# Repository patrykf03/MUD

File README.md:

# The MUD Project

## Warning
**The entire project is untested, use at your own risk and look over whether its not broken beforehand.**

<br/>
The Multiple Universal Daughterboard project is a series of pcb's I've designed to have replaceable modules with microcontrollers.

There are 2 modules based on STM32F411 and nRF microcontrollers.

They can be integrated either by putting an M.2 connector directly on the pcb or connected from a daughterboard over a 30 pin flat ribbon connector.

There are 2 daughterboards currently available.

* Full daughterboard
  * Uses usb C
  * Has a usb Hub with 2 usb A outputs
  * Has an optional magnetic i2c connector
* Simple daughterboard
  *  The same as the full daughterboard but without an integrated hub.

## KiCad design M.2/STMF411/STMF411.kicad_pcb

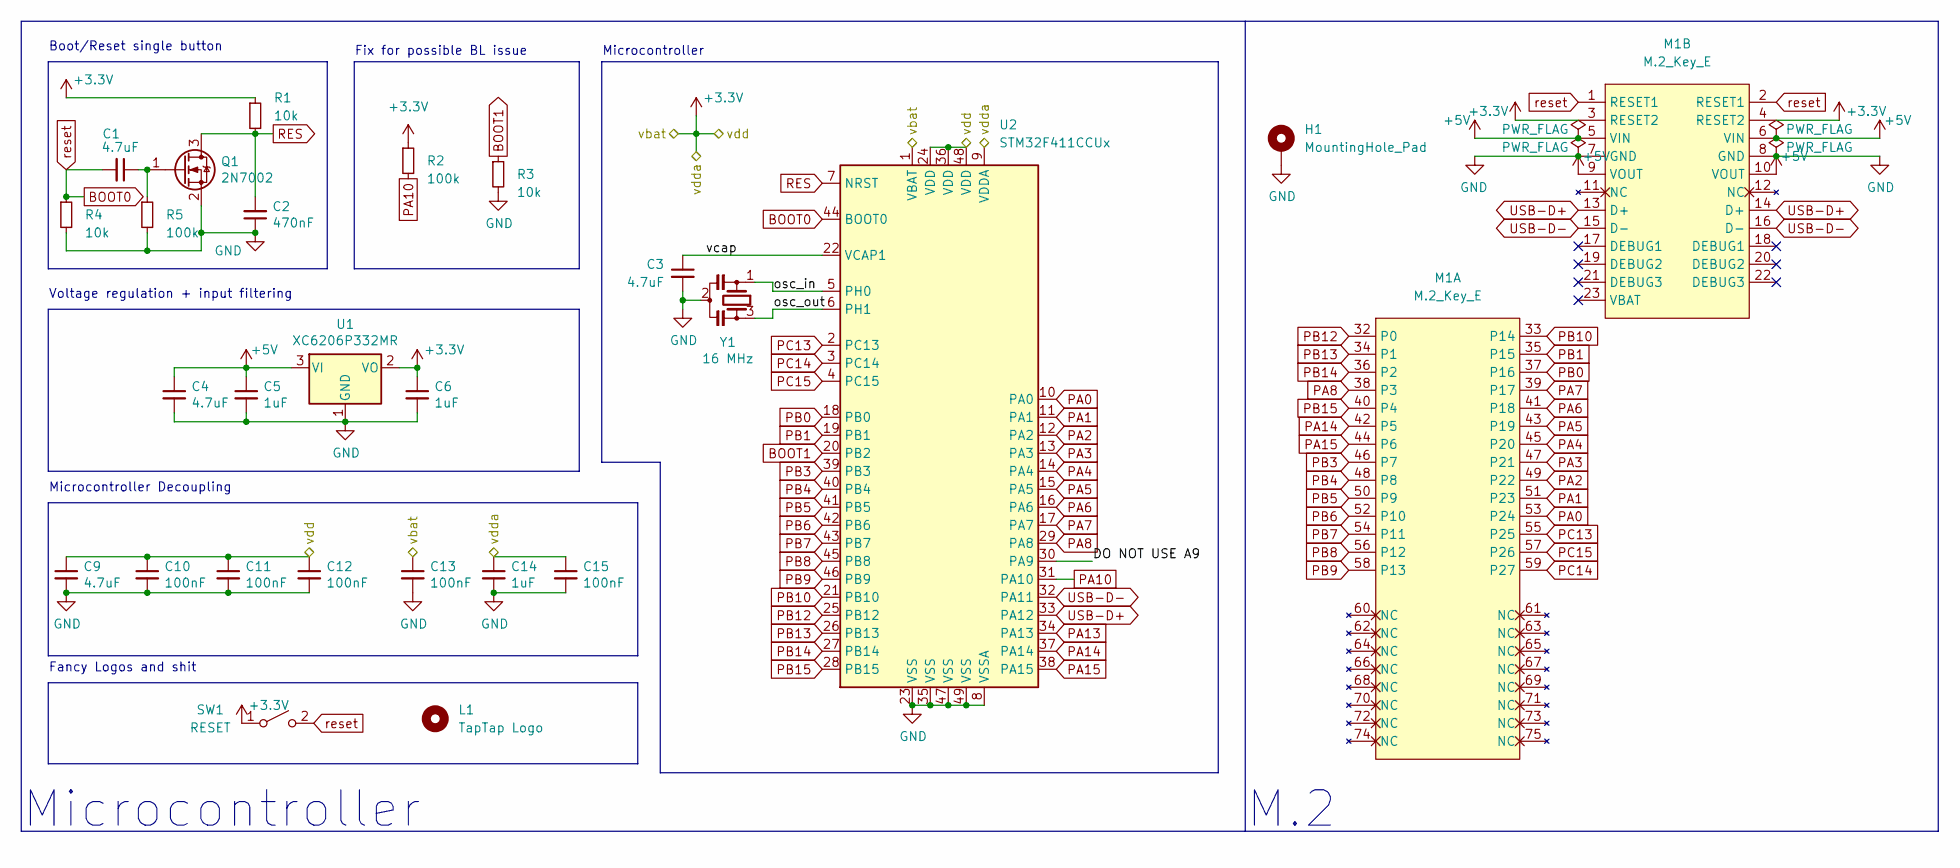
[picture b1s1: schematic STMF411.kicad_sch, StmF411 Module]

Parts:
C1, C3, C4, C9: 4.7uF; C_0402_1005Metric; LCSC C23733
C2: 470nF; C_0402_1005Metric; LCSC C47339
C5, C6, C14: 1uF; C_0402_1005Metric; LCSC C52923
C10, C11, C12, C13, C15: 100nF; C_0402_1005Metric; LCSC C1525
H1: MountingHole_Pad; MountingHole_3.2mm_M3_Pad_Via
L1: TapTap Logo; tt_4mm
M1: M.2_Key_E; m2-padKeyE
Q1: 2N7002; SOT-323_SC-70; LCSC C8545
R1, R3, R4: 10k; R_0402_1005Metric; LCSC C25744
R2, R5: 100k; R_0402_1005Metric; LCSC C25741
SW1: RESET; LogoSmall_Cu
U1: XC6206P332MR; SOT-23; LCSC C5446
U2: STM32F411CCUx; QFN-48-1EP_7x7mm_P0.5mm_EP5.6x5.6mm
Y1: 16 MHz; Resonator_SMD_Murata_CSTxExxV-3Pin_3.0x1.1mm; LCSC C882605

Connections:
+3V3: C6.1, C9.1, C10.1, C11.1, C12.1, C13.1, C14.1, C15.1, M1.3 (RESET2), M1.4 (RESET2), R1.1, R2.1, SW1.1 (A), U1.2 (VO), U2.1 (VBAT), U2.9 (VDDA), U2.24 (VDD), U2.36 (VDD), U2.48 (VDD); also elsewhere on the board
+5V: C4.1, C5.1, M1.5 (VIN), M1.6 (VIN), M1.9 (VOUT), M1.10 (VOUT), U1.3 (VI)
/DO NOT USE A9: U2.30 (PA9)
/osc_in: U2.5 (PH0), Y1.1
/osc_out: U2.6 (PH1), Y1.3
/vcap: C3.1, U2.22 (VCAP1)
BOOT0: C1.2, M1.1 (RESET1), M1.2 (RESET1), R4.1, SW1.2 (B), U2.44 (BOOT0)
BOOT1: R3.1, U2.20 (PB2)
GND: C2.1, C3.2, C4.2, C5.2, C6.2, C9.2, C10.2, C11.2, C12.2, C13.2, C14.2, C15.2, H1.1, M1.7 (GND), M1.8 (GND), Q1.2 (S), R3.2, R4.2, R5.2, U1.1 (GND), U2.8 (VSSA), U2.23 (VSS), U2.35 (VSS), U2.47 (VSS), U2.49 (VSS), Y1.2; also elsewhere on the board
unnamed: C1.1, Q1.1 (G), R5.1
PA0: M1.53 (P24), U2.10 (PA0)
PA1: M1.51 (P23), U2.11 (PA1)
PA2: M1.49 (P22), U2.12 (PA2)
PA3: M1.47 (P21), U2.13 (PA3)
PA4: M1.45 (P20), U2.14 (PA4)
PA5: M1.43 (P19), U2.15 (PA5)
PA6: M1.41 (P18), U2.16 (PA6)
PA7: M1.39 (P17), U2.17 (PA7)
PA8: M1.38 (P3), U2.29 (PA8)
PA10: R2.2, U2.31 (PA10)
PA13: U2.34 (PA13)
PA14: M1.42 (P5), U2.37 (PA14)
PA15: M1.44 (P6), U2.38 (PA15)
PB0: M1.37 (P16), U2.18 (PB0)
PB1: M1.35 (P15), U2.19 (PB1)
PB3: M1.46 (P7), U2.39 (PB3)
PB4: M1.48 (P8), U2.40 (PB4)
PB5: M1.50 (P9), U2.41 (PB5)
PB6: M1.52 (P10), U2.42 (PB6)
PB7: M1.54 (P11), U2.43 (PB7)
PB8: M1.56 (P12), U2.45 (PB8)
PB9: M1.58 (P13), U2.46 (PB9)
PB10: M1.33 (P14), U2.21 (PB10)
PB12: M1.32 (P0), U2.25 (PB12)
PB13: M1.34 (P1), U2.26 (PB13)
PB14: M1.36 (P2), U2.27 (PB14)
PB15: M1.40 (P4), U2.28 (PB15)
PC13: M1.55 (P25), U2.2 (PC13)
PC14: M1.59 (P27), U2.3 (PC14)
PC15: M1.57 (P26), U2.4 (PC15)
RES: C2.2, Q1.3 (D), R1.2, U2.7 (NRST)
USB-D+: M1.13 (D+), M1.14 (D+), U2.33 (PA12)
USB-D-: M1.15 (D-), M1.16 (D-), U2.32 (PA11)

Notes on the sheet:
Microcontroller
Voltage regulation + input filtering
Fancy Logos and shit
Microcontroller Decoupling
M.2
Boot/Reset single button
Fix for possible BL issue

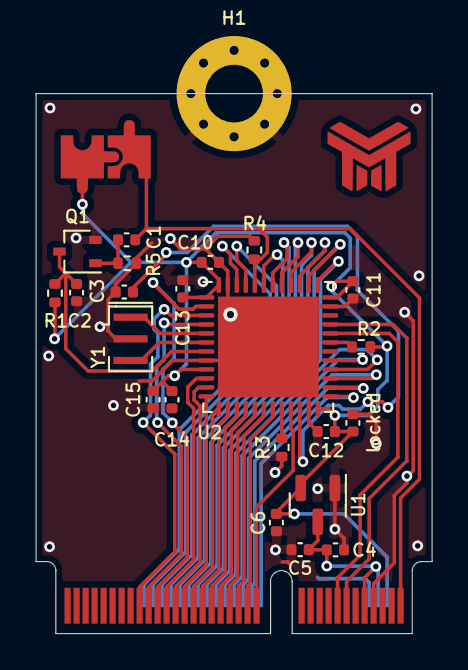
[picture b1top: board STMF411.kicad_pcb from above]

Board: 2 copper layers, 22.0 x 30.0 mm, 27 parts (1 on the bottom side), 41 nets.

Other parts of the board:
Ref**: Val**; text
locked: 4.7uF; C_0402_1005Metric

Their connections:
+3V3: locked.1; also elsewhere on the board
GND: locked.2; also elsewhere on the board

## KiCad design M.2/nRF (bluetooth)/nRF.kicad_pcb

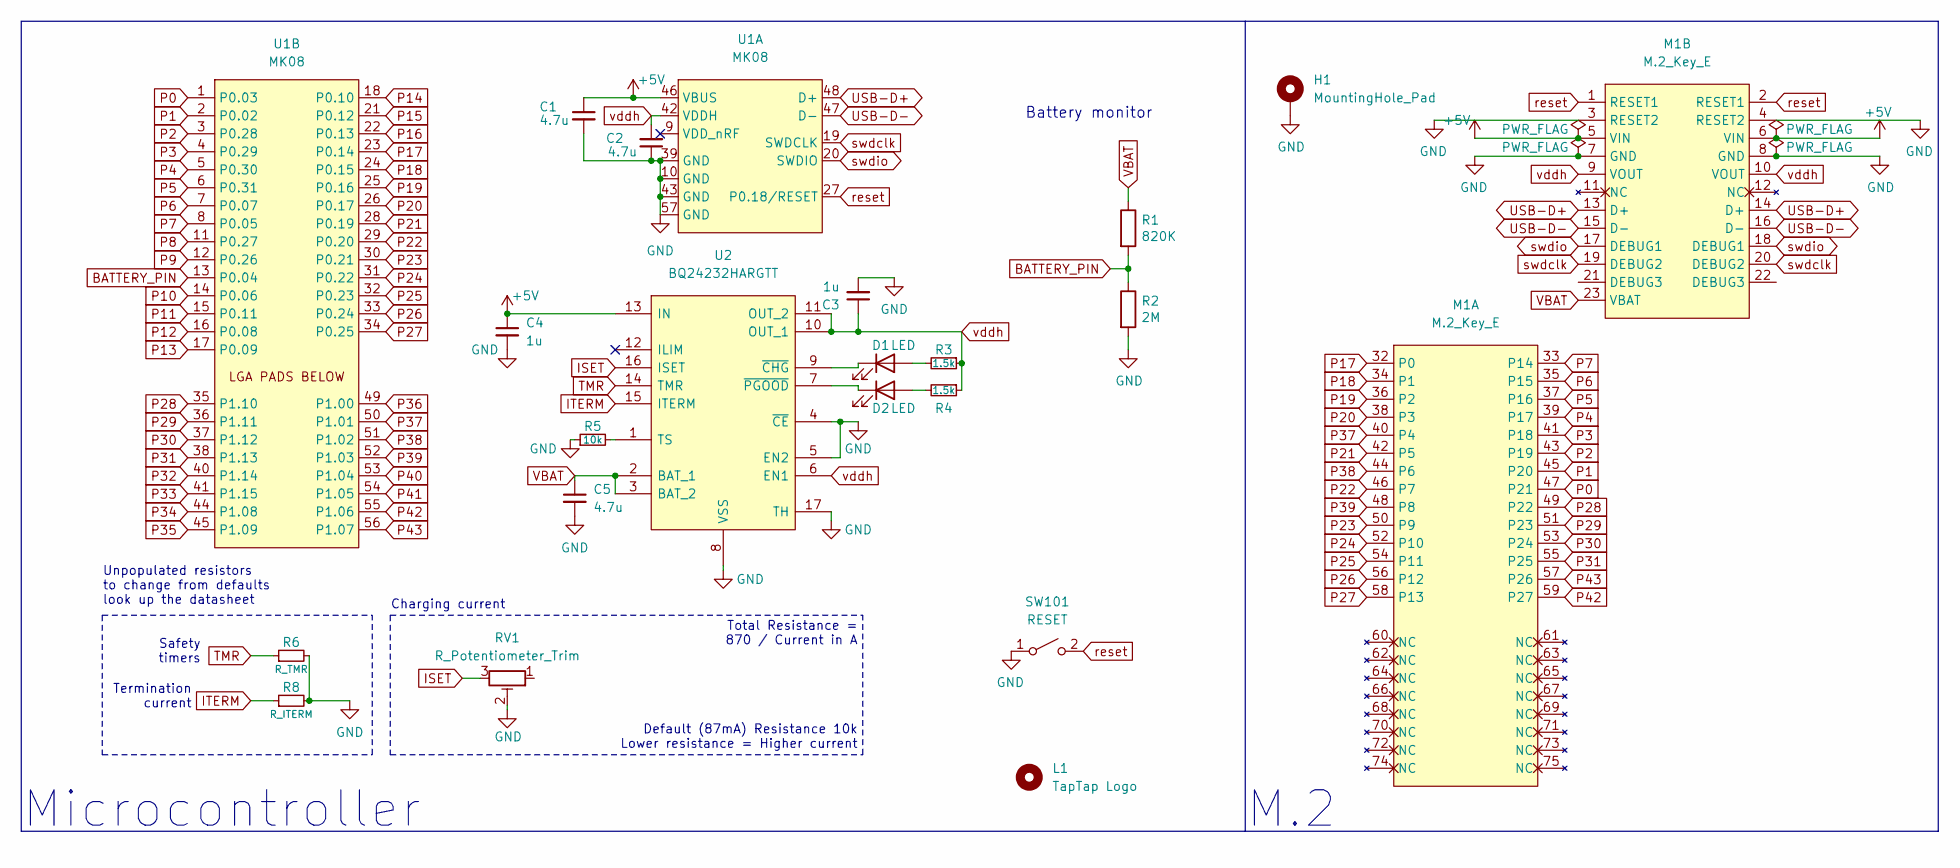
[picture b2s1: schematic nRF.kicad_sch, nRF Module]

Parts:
C1, C2, C5: 4.7u; C_0402_1005Metric
C3, C4: 1u; C_0402_1005Metric
D1, D2: LED; LED_0402_1005Metric
H1: MountingHole_Pad; MountingHole_3.2mm_M3_Pad_Via
L1: TapTap Logo; tt_4mm
M1: M.2_Key_E; m2-padKeyE
R1: 820K; R_0402_1005Metric
R2: 2M; R_0402_1005Metric
R3, R4: 1.5k; R_0402_1005Metric
R5: 10k; R_0402_1005Metric
R6: R_TMR; C_0402_1005Metric
R8: R_ITERM; C_0402_1005Metric
RV1: R_Potentiometer_Trim; Potentiometer_Vishay_TS53YJ_Vertical
SW101: RESET; LogoSmall_Cu
U1: MK08
U2: BQ24232HARGTT; VQFN-16-1EP_3x3mm_P0.5mm_EP1.68x1.68mm_ThermalVias; Manufacturer_Part_Number BQ24232HARGTT; Mouser Part Number 595-BQ24232HARGTT

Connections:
+5V: C1.1, C4.1, M1.5 (VIN), M1.6 (VIN), U1.46 (VBUS), U2.13 (IN)
BATTERY_PIN: R1.2, R2.1, U1.13 (P0.04)
GND: C1.2, C2.1, C3.2, C4.2, C5.2, H1.1, M1.3 (RESET2), M1.4 (RESET2), M1.7 (GND), M1.8 (GND), R2.2, R5.1, R6.2, R8.2, RV1.2, SW101.1 (A), U1.10 (GND), U1.39 (GND), U1.43 (GND), U1.57 (GND), U2.4 (~CE), U2.5 (EN2), U2.8 (VSS), U2.17 (TH)
ISET: RV1.3, U2.16 (ISET)
ITERM: R8.1, U2.15 (ITERM)
unnamed: D1.1 (K), U2.9 (~CHG)
unnamed: D1.2 (A), R3.2
unnamed: D2.1 (K), U2.7 (~PGOOD)
unnamed: D2.2 (A), R4.2
unnamed: R5.2, U2.1 (TS)
P0: M1.47 (P21), U1.1 (P0.03)
P1: M1.45 (P20), U1.2 (P0.02)
P2: M1.43 (P19), U1.3 (P0.28)
P3: M1.41 (P18), U1.4 (P0.29)
P4: M1.39 (P17), U1.5 (P0.30)
P5: M1.37 (P16), U1.6 (P0.31)
P6: M1.35 (P15), U1.7 (P0.07)
P7: M1.33 (P14), U1.8 (P0.05)
P8: U1.11 (P0.27)
P9: U1.12 (P0.26)
P10: U1.14 (P0.06)
P11: U1.15 (P0.11)
P12: U1.16 (P0.08)
P13: U1.17 (P0.09)
P14: U1.18 (P0.10)
P15: U1.21 (P0.12)
P16: U1.22 (P0.13)
P17: M1.32 (P0), U1.23 (P0.14)
P18: M1.34 (P1), U1.24 (P0.15)
P19: M1.36 (P2), U1.25 (P0.16)
P20: M1.38 (P3), U1.26 (P0.17)
P21: M1.42 (P5), U1.28 (P0.19)
P22: M1.46 (P7), U1.29 (P0.20)
P23: M1.50 (P9), U1.30 (P0.21)
P24: M1.52 (P10), U1.31 (P0.22)
P25: M1.54 (P11), U1.32 (P0.23)
P26: M1.56 (P12), U1.33 (P0.24)
P27: M1.58 (P13), U1.34 (P0.25)
P28: M1.49 (P22), U1.35 (P1.10)
P29: M1.51 (P23), U1.36 (P1.11)
P30: M1.53 (P24), U1.37 (P1.12)
P31: M1.55 (P25), U1.38 (P1.13)
P32: U1.40 (P1.14)
P33: U1.41 (P1.15)
P34: U1.44 (P1.08)
P35: U1.45 (P1.09)
P36: U1.49 (P1.00)
P37: M1.40 (P4), U1.50 (P1.01)
P38: M1.44 (P6), U1.51 (P1.02)
P39: M1.48 (P8), U1.52 (P1.03)
P40: U1.53 (P1.04)
P41: U1.54 (P1.05)
P42: M1.59 (P27), U1.55 (P1.06)
P43: M1.57 (P26), U1.56 (P1.07)
TMR: R6.1, U2.14 (TMR)
USB-D+: M1.13 (D+), M1.14 (D+), U1.48 (D+)
USB-D-: M1.15 (D-), M1.16 (D-), U1.47 (D-)
VBAT: C5.1, M1.23 (VBAT), R1.1, U2.2 (BAT_1), U2.3 (BAT_2)
reset: M1.1 (RESET1), M1.2 (RESET1), SW101.2 (B), U1.27 (P0.18/RESET)
swdclk: M1.19 (DEBUG2), M1.20 (DEBUG2), U1.19 (SWDCLK)
swdio: M1.17 (DEBUG1), M1.18 (DEBUG1), U1.20 (SWDIO)
vddh: C2.2, C3.1, M1.9 (VOUT), M1.10 (VOUT), R3.1, R4.1, U1.42 (VDDH), U2.6 (EN1), U2.10 (OUT_1), U2.11 (OUT_2)

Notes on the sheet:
Termination current
Unpopulated resistors to change from defaults look up the datasheet
Safety timers
Total Resistance = 870 / Current in A
Battery monitor
Charging current
Default (87mA) Resistance 10k Lower resistance = Higher current
Microcontroller
M.2

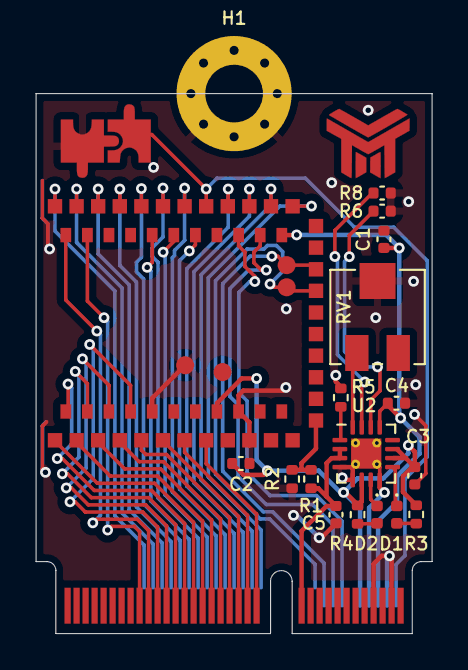
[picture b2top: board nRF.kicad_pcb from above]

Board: 2 copper layers, 22.0 x 30.0 mm, 22 parts (1 on the bottom side), 46 nets.

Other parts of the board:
Ref**: Val**; text

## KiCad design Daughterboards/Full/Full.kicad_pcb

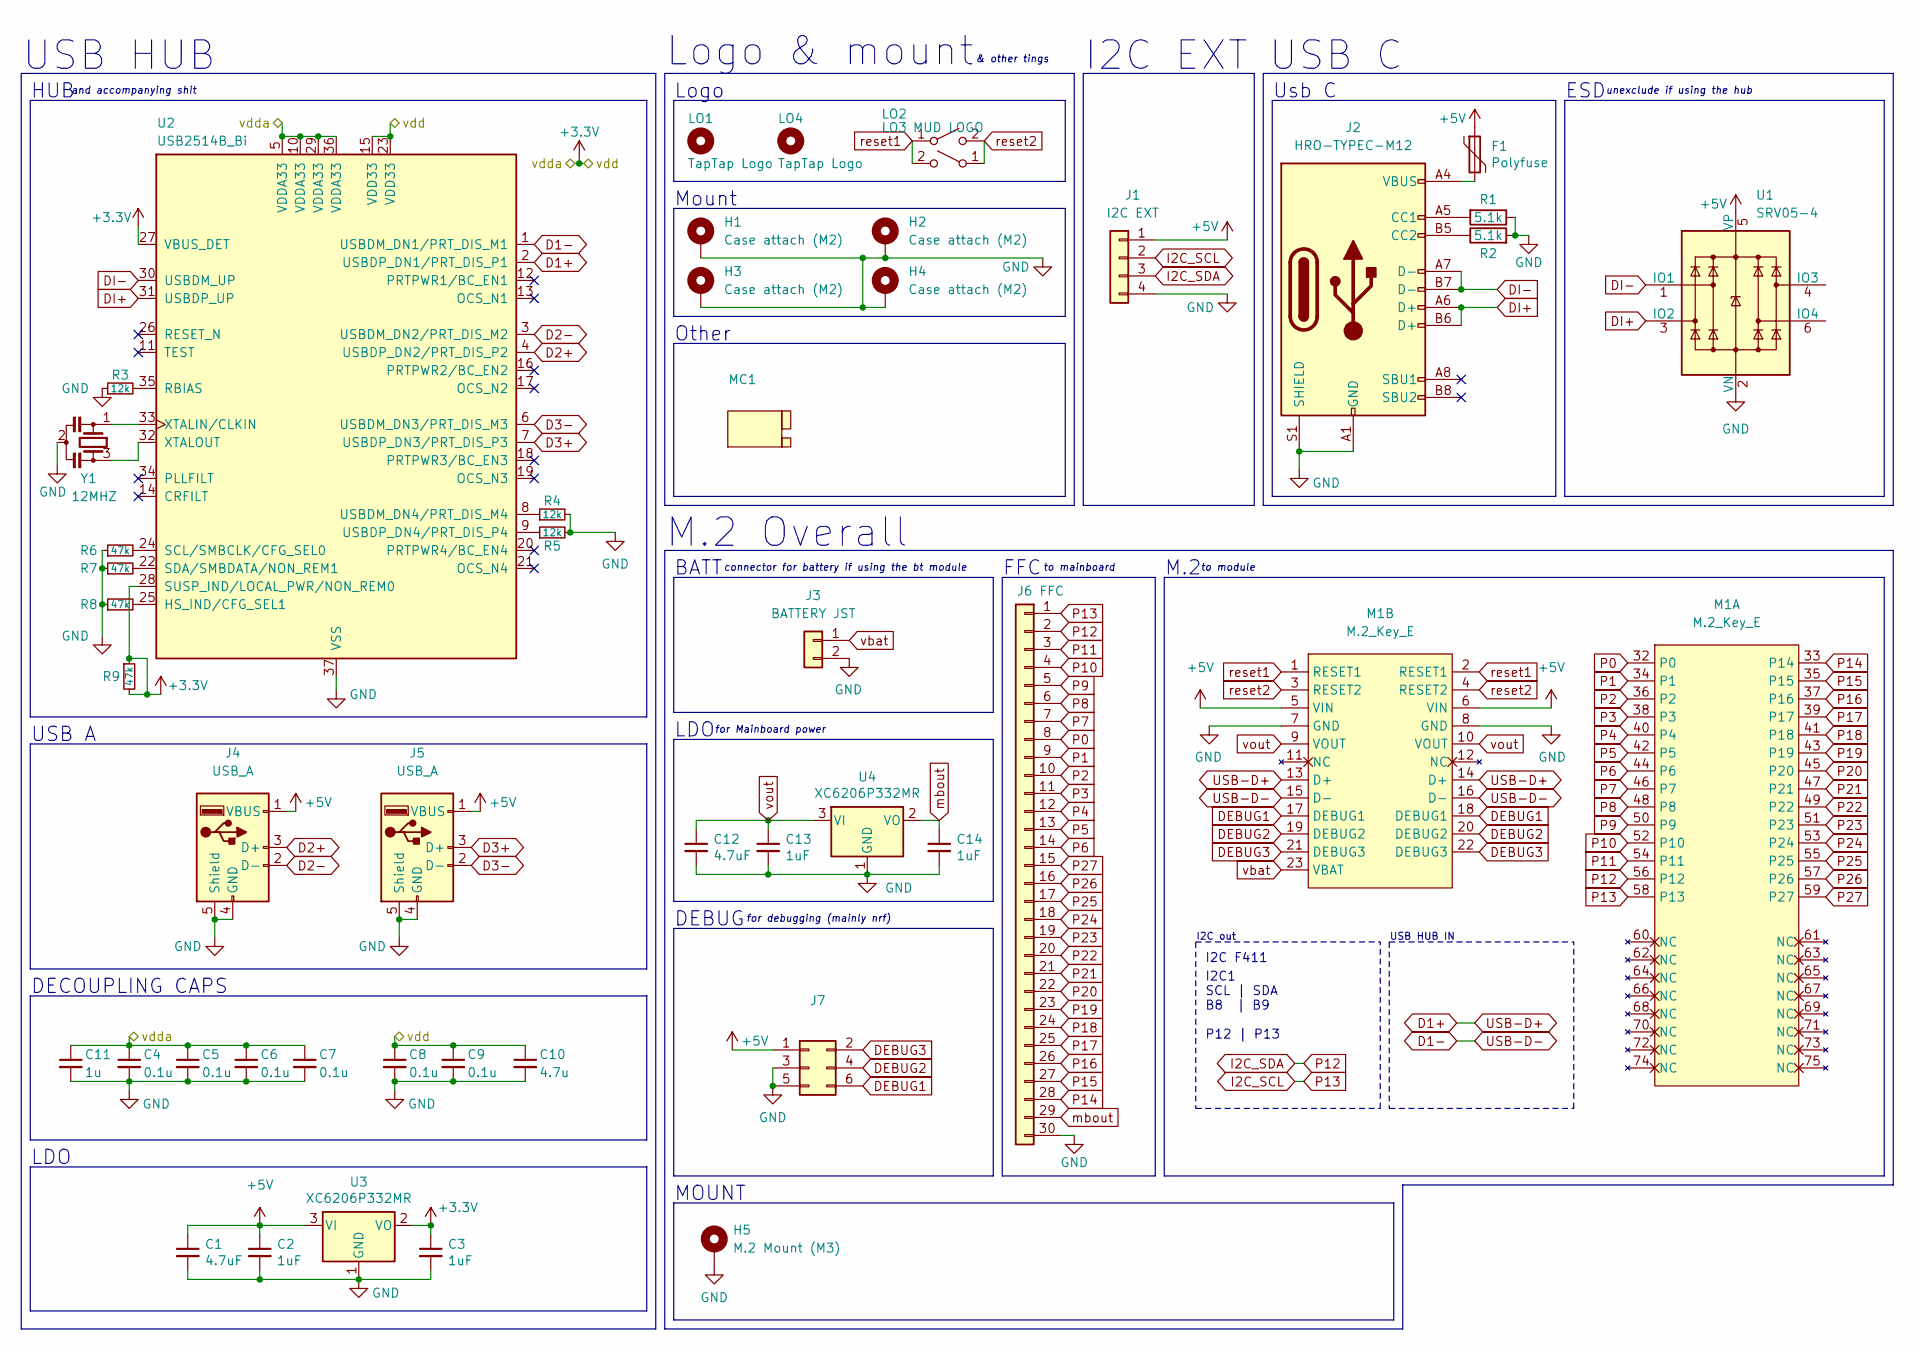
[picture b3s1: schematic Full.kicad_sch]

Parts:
C1, C12: 4.7uF; C_0402_1005Metric; LCSC C23733
C2, C3, C13, C14: 1uF; C_0402_1005Metric; LCSC C52923
C4, C5, C6, C7, C8, C9: 0.1u; C_0402_1005Metric
C10: 4.7u; C_0402_1005Metric
C11: 1u; C_0402_1005Metric
F1: Polyfuse; R_0805_2012Metric
H1, H2, H3, H4: Case attach (M2); MountingHole_2.2mm_M2_Pad
H5: M.2 Mount (M3); MountingHole_3.2mm_M3_DIN965_Pad
J1: I2C EXT; Magnetic Pogo 4 pin
J2: HRO-TYPEC-M12; USB_C_Receptacle_HRO_TYPE-C-31-M-12
J3: BATTERY JST; JST_PH_S2B-PH-SM4-TB_1x02-1MP_P2.00mm_Horizontal
J4, J5: USB_A; USB_A_Stewart_SS-52100-001_Horizontal
J6: FFC; 100519223010ELF
J7: PinSocket_2x03_P2.54mm_Vertical
LO1, LO4: TapTap Logo; tt_4mm
LO2: (no value)
LO3: MUD LOGO; LogoSmall_Cu
M1: M.2_Key_E; m2-bracket-key-e
MC1: (no value)
R1, R2: 5.1k; R_0402_1005Metric
R3, R4, R5: 12k; R_0402_1005Metric
R6, R7, R8, R9: 47k; R_0402_1005Metric
U1: SRV05-4; SOT-23-6
U2: USB2514B_Bi; QFN-36-1EP_6x6mm_P0.5mm_EP3.7x3.7mm_ThermalVias
U3, U4: XC6206P332MR; SOT-23; LCSC C5446
Y1: 12MHZ; Resonator_SMD_Murata_CSTxExxV-3Pin_3.0x1.1mm

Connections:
+3V3: C3.1, C4.1, C5.1, C6.1, C7.1, C8.1, C9.1, C10.1, C11.1, R9.1, R9.2, U2.5 (VDDA33), U2.10 (VDDA33), U2.15 (VDD33), U2.23 (VDD33), U2.27 (VBUS_DET), U2.28 (SUSP_IND/LOCAL_PWR/NON_REM0), U2.29 (VDDA33), U2.36 (VDDA33), U3.2 (VO)
+5V: C1.1, C2.1, F1.1, J1.1, J4.1 (VBUS), J5.1 (VBUS), J7.1, M1.5 (VIN), M1.6 (VIN), U1.5 (VP), U3.3 (VI)
D1+: M1.13 (D+), M1.14 (D+), U2.2 (USBDP_DN1/PRT_DIS_P1)
D1-: M1.15 (D-), M1.16 (D-), U2.1 (USBDM_DN1/PRT_DIS_M1)
D2+: J4.3 (D+), U2.4 (USBDP_DN2/PRT_DIS_P2)
D2-: J4.2 (D-), U2.3 (USBDM_DN2/PRT_DIS_M2)
D3+: J5.3 (D+), U2.7 (USBDP_DN3/PRT_DIS_P3)
D3-: J5.2 (D-), U2.6 (USBDM_DN3/PRT_DIS_M3)
DEBUG1: J7.6, M1.17 (DEBUG1), M1.18 (DEBUG1)
DEBUG2: J7.4, M1.19 (DEBUG2), M1.20 (DEBUG2)
DEBUG3: J7.2, M1.21 (DEBUG3), M1.22 (DEBUG3)
DI+: J2.A6 (D+), J2.B6 (D+), U1.3 (IO2), U2.31 (USBDP_UP)
DI-: J2.A7 (D-), J2.B7 (D-), U1.1 (IO1), U2.30 (USBDM_UP)
GND: C1.2, C2.2, C3.2, C4.2, C5.2, C6.2, C7.2, C8.2, C9.2, C10.2, C11.2, C12.2, C13.2, C14.2, H1.1, H2.1, H3.1, H4.1, H5.1, J1.4, J2.A1 (GND), J2.A12 (GND), J2.B1 (GND), J2.B12 (GND), J2.S1 (SHIELD), J3.2, J4.4 (GND), J4.5 (Shield), J5.4 (GND), J5.5 (Shield), J6.30, J7.3, J7.5, M1.7 (GND), M1.8 (GND), R1.1, R2.2, R3.1, R4.2, R5.2, R6.1, R7.1, R8.1, U1.2 (VN), U2.37 (VSS), U3.1 (GND), U4.1 (GND), Y1.2
I2C_SCL: J1.2, J6.1, M1.58 (P13)
I2C_SDA: J1.3, J6.2, M1.56 (P12)
unnamed: F1.2, J2.A4 (VBUS), J2.A9 (VBUS), J2.B4 (VBUS), J2.B9 (VBUS)
unnamed: J2.A5 (CC1), R1.2
unnamed: J2.B5 (CC2), R2.1
unnamed: R3.2, U2.35 (RBIAS)
unnamed: R4.1, U2.8 (USBDM_DN4/PRT_DIS_M4)
unnamed: R5.1, U2.9 (USBDP_DN4/PRT_DIS_P4)
unnamed: R6.2, U2.24 (SCL/SMBCLK/CFG_SEL0)
unnamed: R7.2, U2.22 (SDA/SMBDATA/NON_REM1)
unnamed: R8.2, U2.25 (HS_IND/CFG_SEL1)
unnamed: U2.32 (XTALOUT), Y1.3
unnamed: U2.33 (XTALIN/CLKIN), Y1.1
P0: J6.8, M1.32 (P0)
P1: J6.9, M1.34 (P1)
P2: J6.10, M1.36 (P2)
P3: J6.11, M1.38 (P3)
P4: J6.12, M1.40 (P4)
P5: J6.13, M1.42 (P5)
P6: J6.14, M1.44 (P6)
P7: J6.7, M1.46 (P7)
P8: J6.6, M1.48 (P8)
P9: J6.5, M1.50 (P9)
P10: J6.4, M1.52 (P10)
P11: J6.3, M1.54 (P11)
P14: J6.28, M1.33 (P14)
P15: J6.27, M1.35 (P15)
P16: J6.26, M1.37 (P16)
P17: J6.25, M1.39 (P17)
P18: J6.24, M1.41 (P18)
P19: J6.23, M1.43 (P19)
P20: J6.22, M1.45 (P20)
P21: J6.21, M1.47 (P21)
P22: J6.20, M1.49 (P22)
P23: J6.19, M1.51 (P23)
P24: J6.18, M1.53 (P24)
P25: J6.17, M1.55 (P25)
P26: J6.16, M1.57 (P26)
P27: J6.15, M1.59 (P27)
mbout: C14.1, J6.29, U4.2 (VO)
reset1: LO2.1 (A), LO3.2 (B), M1.1 (RESET1), M1.2 (RESET1)
reset2: LO2.2 (B), LO3.1 (A), M1.3 (RESET2), M1.4 (RESET2)
vbat: J3.1, M1.23 (VBAT)
vout: C12.1, C13.1, M1.9 (VOUT), M1.10 (VOUT), U4.3 (VI)

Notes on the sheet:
to module
Mount
for debugging (mainly nrf)
HUB
I2C out
BATT
to mainboard
M.2
unexclude if using the hub
LDO
DECOUPLING CAPS
USB HUB IN
FFC
Usb C
Logo
for Mainboard power
I2C EXT
I2C F411
M.2 Overall
and accompanying shit
connector for battery if using the bt module
ESD
Logo & mount
USB A
& other tings
Other
DEBUG
USB C
MOUNT
USB HUB
I2C1 SCL | SDA B8 | B9 P12 | P13

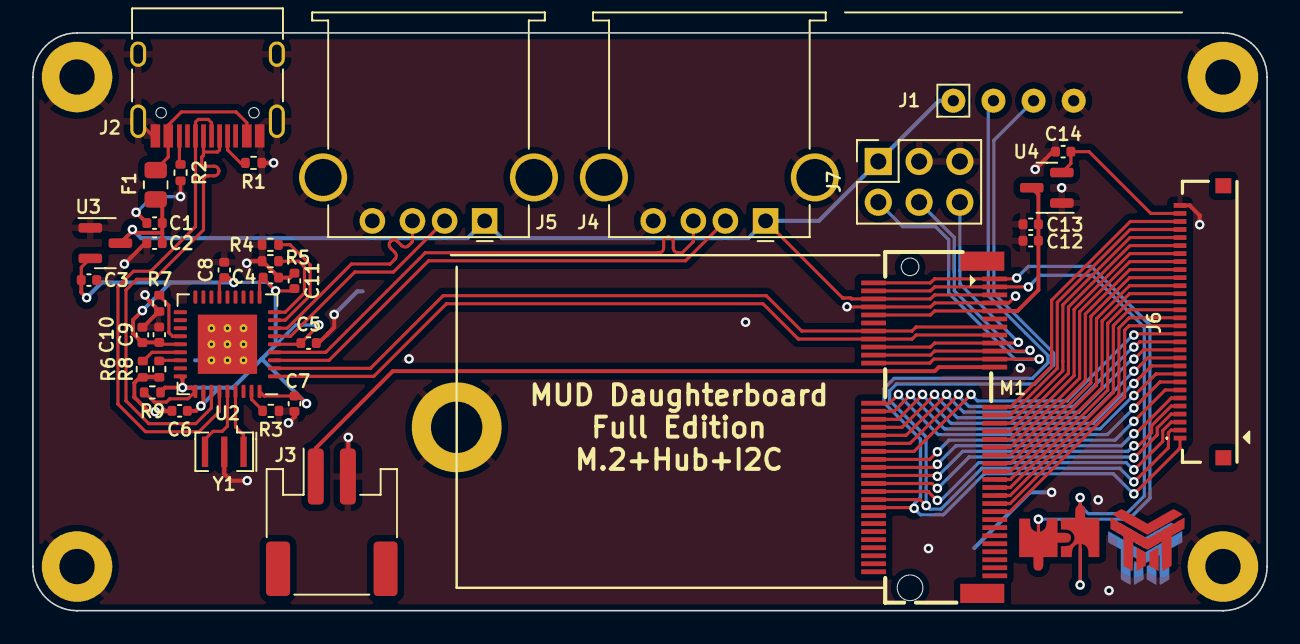
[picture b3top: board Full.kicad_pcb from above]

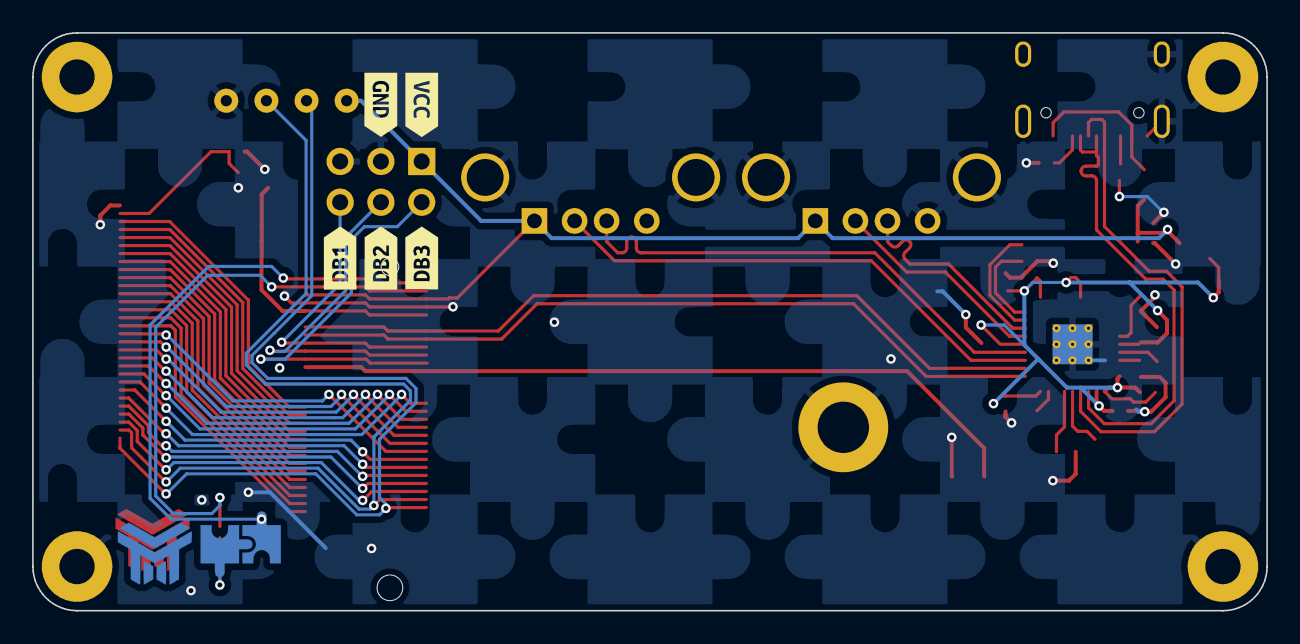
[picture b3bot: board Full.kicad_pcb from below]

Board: 2 copper layers, 76.9 x 36.0 mm, 51 parts (7 on the bottom side), 58 nets.

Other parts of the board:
Ref**: Val**; Full-brd
kibuzzard-623B2553: G***; kibuzzard-623B2553
kibuzzard-623B2559: G***; kibuzzard-623B2559
kibuzzard-623B2562: G***; kibuzzard-623B2562
kibuzzard-623B2578: G***; kibuzzard-623B2578
kibuzzard-623B2586: G***; kibuzzard-623B2586

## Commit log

2022-03-11 Create LICENSE
2022-03-11 add submodules
2022-03-11 change kicad ngff to my fork for future edits
2022-03-12 add M.2 tempfile and markdown files for dirs
2022-03-12 update the m.2 library
2022-03-14 Add the files for different M.2 Boards and work on STM32F411
2022-03-15 finish f411 and change it to key e
2022-03-15 change the rest to key e, change the template
2022-03-15 finish working on stmf411
2022-03-15 add gitignore
2022-03-16 add bluetooth m.2 carrier schematics and accompanying things
2022-03-16 add moko submodule and update marbastlib
2022-03-16 add moko properly
2022-03-18 last touchups to nRF
2022-03-18 touchups to f411
2022-03-18 remove RP2040 and template
2022-03-18 finalize f411 for the last time. change to sot-23 ldo
2022-03-18 add teardrops to nrf
2022-03-18 Fix gitignore
    Ignore bakcups
2022-03-18 remove tracking for bakcup zips
2022-03-18 remove tracking for other shit
2022-03-20 change vout on nRF to system out from the powerpath
2022-03-20 start working on the daughterboards
2022-03-20 some fixes
2022-03-22 add new 3d models
2022-03-22 untrack backups
2022-03-22 change gitignore to include more exclusions for bk
2022-03-22 change shit in libraries
2022-03-22 change stm to use 5v instead of 3.3v on vout
2022-03-22 major progress on the full db
2022-03-23 more 3d models
2022-03-23 connect the ffc to the m.2 on the full
2022-03-23 add new logo. add full back logo thingie
2022-03-23 finish the full db
2022-03-23 add m.2 module step
2022-03-23 update m2ngff lib
2022-03-25 change magnetic pogo around thinger
2022-03-25 fix the puzzle back after i accidentally removed it
2022-03-25 add simple db
2022-03-25 change modules to new logo
2022-03-25 add some docs
2022-03-25 remove docs dir as it was useless
2022-03-25 remove backups and fix gitignore because i forgot
2022-03-25 add iss pcb as a submodule
2022-03-25 update submodules and sub cfg
2022-03-26 prettify files a lil bit
2022-03-26 change marbastlib to untested
2022-03-26 add mxhybrid library
2022-03-26 add 3d models
2022-03-28 add 8 pin ffc + 3d model
2022-03-28 add soft symlink to point to the 3d for marbastlib links
2022-03-28 update kicad-m2ngff with the changes
2022-03-28 start working on ISS
2022-03-29 update iss
2022-03-30 do stuff
2022-03-30 add new iss
2022-04-01 add new 3dmodels
2022-04-01 change shit in m.2
2022-04-01 add rev iso stab footprint
2022-04-02 add finalised iss and update ngff lib
2023-05-11 change up logo's to nicer ones on modules, update iss
2023-05-11 Add warning
